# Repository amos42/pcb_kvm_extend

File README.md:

# KVM 확장 보드

---

[ATX switch 제어 보드](kvm_switch/)
([README.md](kvm_switch/README.md))

---

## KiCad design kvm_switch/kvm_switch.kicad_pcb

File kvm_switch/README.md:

# KVM Switch Board

### 회로도

### PCB

### PCB 샘플 이미지

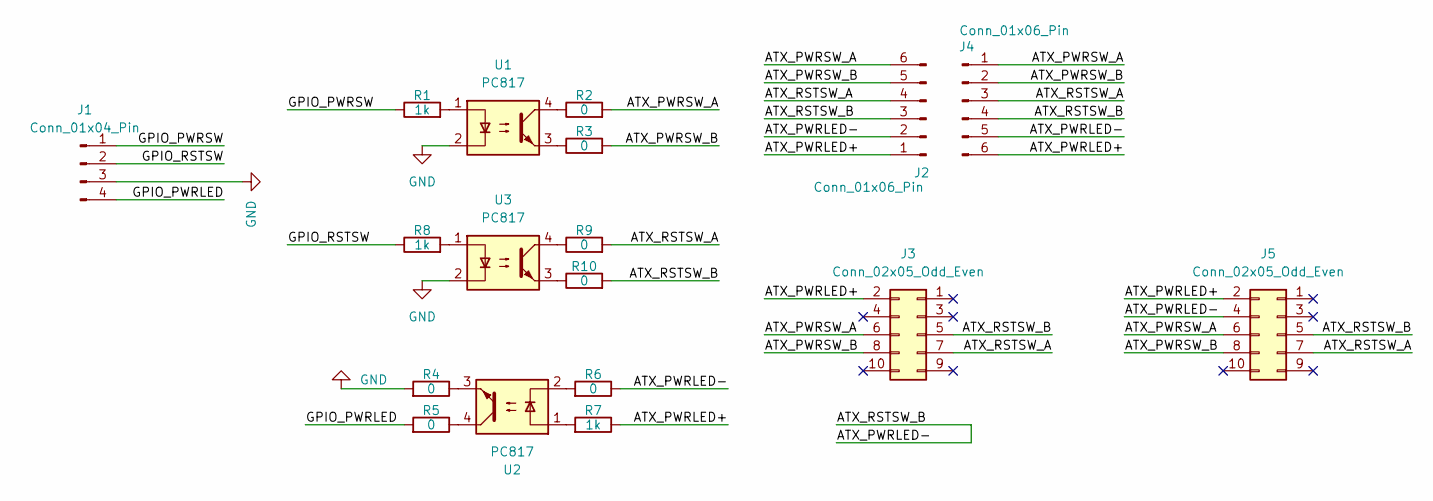
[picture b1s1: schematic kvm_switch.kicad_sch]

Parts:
J1: Conn_01x04_Pin; Molex_PicoBlade_53047-0410_1x04_P1.25mm_Vertical
J2, J4: Conn_01x06_Pin; Molex_PicoBlade_53047-0610_1x06_P1.25mm_Vertical
J3: Conn_02x05_Odd_Even; PinSocket_2x05_P2.00mm_Vertical
J5: Conn_02x05_Odd_Even; PinSocket_2x05_P2.54mm_Vertical
R1, R7, R8: 1k; R_0805_2012Metric_Pad1.20x1.40mm_HandSolder
R2, R3, R4, R5, R6, R9, R10: 0; R_0805_2012Metric_Pad1.20x1.40mm_HandSolder
U1, U2, U3: PC817; SSO-4_6.7x5.1mm_P2.54mm_Clearance8mm

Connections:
/ATX_PWRLED+: J2.1, J3.2, J4.6, J5.2, R7.1
/ATX_PWRLED-: J2.2, J2.3, J3.5, J4.4, J4.5, J5.4, J5.5, R6.1, R10.2
/ATX_PWRSW_A: J2.6, J3.6, J4.1, J5.6, R2.2
/ATX_PWRSW_B: J2.5, J3.8, J4.2, J5.8, R3.2
/ATX_RSTSW_A: J2.4, J3.7, J4.3, J5.7, R9.2
/GPIO_PWRLED: J1.4, R5.2
/GPIO_PWRSW: J1.1, R1.1
/GPIO_RSTSW: J1.2, R8.1
GND: J1.3, R4.2, U1.2, U3.2
unnamed: R1.2, U1.1
unnamed: R2.1, U1.4
unnamed: R3.1, U1.3
unnamed: R4.1, U2.3
unnamed: R5.1, U2.4
unnamed: R6.2, U2.2
unnamed: R7.2, U2.1
unnamed: R8.2, U3.1
unnamed: R9.1, U3.4
unnamed: R10.1, U3.3

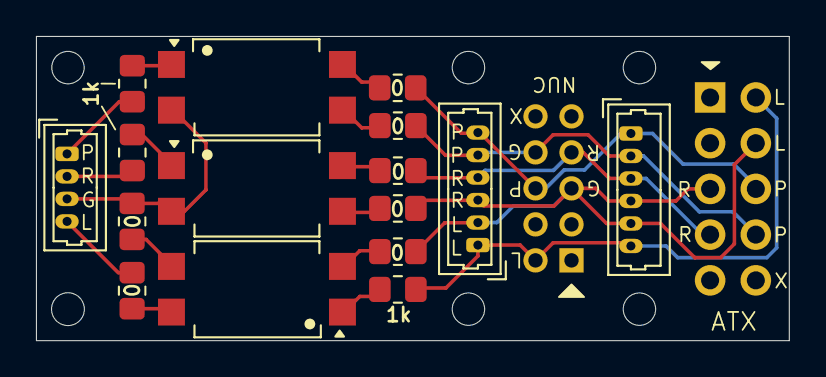
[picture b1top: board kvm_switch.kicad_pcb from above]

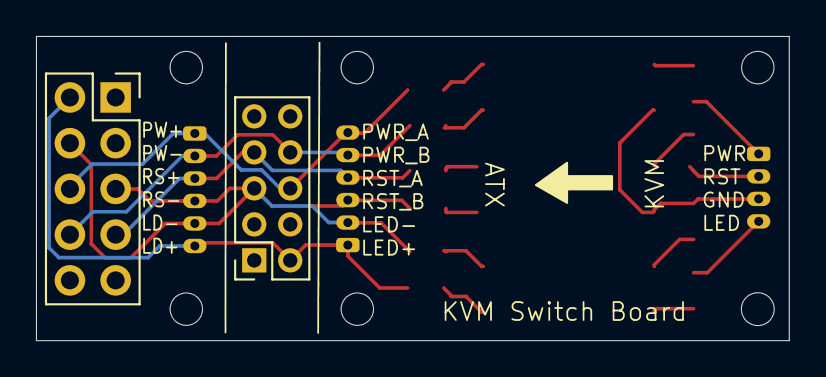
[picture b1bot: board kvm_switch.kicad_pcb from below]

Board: 2 copper layers, 41.8 x 16.9 mm, 18 parts (2 on the bottom side), 19 nets.

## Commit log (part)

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2025-05-12 이미지 편집
2025-05-15 1차 주문 본
2025-05-16 마커 보강
